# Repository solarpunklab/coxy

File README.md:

<div align="center">
<!-- ## SOLARPUNKLAB - CoXY -->

<!-- PROJECT LOGO -->

</div>

<br>

<div align="left" width = 90% id="contents">
<!-- TABLE OF CONTENTS -->
<details open>
  <summary style="background-color: #aaa;"><b>CONTENTS</b></summary>
  <ul>
	<li><a href="#about">About CoXY<br></a></li>
	<li><a href="#coxy-hardware">CoXY Hardware<br></a></li>
	<li><a href="#coxy-software">CoXY Sofwtare<br></a></li>
  </ul>
  </details>
</div>

<br><br><hr> <br><br>

<!-- >>>>>> TABLE ABOUT CoXY <<<<< -->
<table width = 90%>
<tr>
<td align = "justify" width = 90% colspan=2>
<p align="justify" id="about">
<b>ABOUT CoXY</b>
<br><br>
CoXY is a project by TeZ of 
<a href="http://solarpunklab.org">SOLARPUNK LAB</a> / 
<a href="http://hackteria.org">HACKTERIA</a> 
aimed at designing and experimenting a combined hardware and software platform that can function as a test bed for sensors' data monitoring/visualization and automation control, including motors, lights, switches and/or anything that can be driven by transistors. 
<br><br>

<br><br>
The concept arose from the collaborative efforts of Marc Dusseiller Dusjagr  and Fernando Castro, both affiliated with HACKTERIA. Their inspiration stemmed from their involvement in the GOSH Open Hardware project, where they jointly explored the design and creation of a DIY platform for Soil Respiration Chamber(SRC). See <a href="https://hackteria.org/wiki/CO2_Soil_Respiration_Chamber">Hackteria Wiki</a> for an extended overview and documentation.
<br><br>

<br><br>
TeZ and Marc reconstructed a SRC prototype at Solarpunk Lab headquarters in Amsterdam. Subsequently, TeZ embarked on experimenting with an expanded version, aiming to incorporate local sensor data monitoring via WiFi/websockets technology and mechanical parts control using motors. 
<br><br>

<br>

<br><br>
TeZ designed a printed circuit board (PCB) capable of seamlessly daisy-chaining up to five I2C devices. Additionally, it enables control over 8 channels of analog electrical signals via a transistor array IC. This is ideal to easily control the 2 coils of a 28byj-48 stepper motor with 4 channels. The PCB also features breakout options for additional ESP32 I/O pins and voltage supply.
<br><br>
</a>
This first version of the PCB is paired with a browser-based (hence cross-platform) software application, highly customizable and flexible.

<br><br>

<br><br>

<a href="#contents"></A>
<br>
</tr>
</table>

 <!-- >>>>>> TABLE CoXY HARDWARE <<<<< -->
<table width = 90%>
<tr>
<td align = "justify" width = 90% colspan=2>
<p align="justify" id="coxy-hardware">
<b>CoXY HARDWARE</b>
<br><br>
</a>
<br>
first working proto board

CoXY's test bed consists of a Lolin S2 mini ESP32 board expander that can directly interface to a ULN2803 darlington trasistor array and to the I2C bus with five onboard channels. More S2 i/o pins are exposed to connect other analog or one-wire sensors and actuators.
<br><br>
While the CoXY board was designed to reproduce a setup for Soil Respiration Chamber(s), this circuit can facilitate all kind of projects that make use of up to five I2C peripherals and up to 8 low power transistor controlled devices. The adoption of Lolin S2 Mini ESP32 board is very advantageous for the minimal size of this microcontroller, its power, the many number of i/o pins and the very convenient price too.
<br><br>

<br><br>
</tr>

<tr>

<td align = "left" width = 90% colspan=2>
<b>PARTS</b>
<br><br>
The test bed of choice for CoXY comprises:

<ul>
<li> Lolin S2 mini ESP32
<li> ULN2803 transistor array IC
<li> 28BYJ-48 stepper motor
<li> SENSIRION SCD41 - I2C Carbon Dioxide, temperature and humidity sensor
<li> BME680 - I2C temperature, humidity, pressure and gas sensor
<li> DALLAS DS18b20 "one-wire" Temperature sensor
<li> SSD1306 - 128x64 - I2C OLED display
</ul>

All parts are "optional" and can be excluded from the setup by simply commenting the #define statements in the main.cpp code. 
<br><br>
The <a href="https://github.com/GenericLab/UROS-CO2_brkout">UROS breakout</a> board was kindly provided by Marc to support the development of this project and it features also an optional connection to a NEOPIXEL rgb led unit.
<br><br>
Below all images and links to source the individual parts.
<br><br>
<nr>
LOLIN S2 Mini ESP32
<br><br>
<a href="https://nl.aliexpress.com/item/32461441516.html"><br>
ULN2803  - Bipolar (BJT) Transistor Array 8 NPN Darlington 50V 500mA </a>
<br><br>
<a href="https://nl.aliexpress.com/item/1005006141716201.html"><br>
28BYJ-48 5V stepper motor</a>
<br><br>
<a href="https://nl.aliexpress.com/item/1005006387743045.html"><br>
SCD41  I2C Carbon Dioxide, Temperature And Humidity sensor</a>
<br><br>
<a href="https://github.com/GenericLab/UROS-CO2_brkout"><br>
first SCD41 UROS breakout</a>
<br><br>
<a href="https://github.com/solarpunklab/coxy/tree/main/PCB/CO2Y-brkout"><br>
 new SCD41 CO2Y breakout</a> designed by TeZ and Marc in 2024
<br><br>
<a href="https://nl.aliexpress.com/item/1005001602441073.html"><br>
BME680 Digital Temperature, Humidity, Pressure, Gas Sensor </a>
<br><br>

<a href="https://nl.aliexpress.com/item/32676135779.html"><br>
DALLAS DS18b20 "one-wire" Temperature sensor</a>
<br><br>

<a href="https://nl.aliexpress.com/item/1005006141235306.html"><br>
SSD1306 - 128x64 - I2C OLED display</a>
<br><br>

<hr>

CoXY BOARD is a PCB designed by TeZ and currently in testing phase. More details and photos will be published soon.

<br>

<br>

<br><br>

<br><br>

<br><br>

<br><br>

<br><br>

<br><br>

<br>
<hr>
<br>
<a href="STL/CoxyBoxy.stl" target="3d"></A>
<br>
<a href="STL/CoxyBoxy-top.stl" target="3d"></A>
<br><br>
<a href="#contents"></A>
<br>

</td>
<br>
</tr>
</table>

<!-- >>>>>> TABLE CoXY SOFTWARE<<<<< -->
<table width = 90%>
<tr>
<td align = "justify" width = 90% colspan=2>
<p align="justify" id="coxy-software">
<b>CoXY SOFTWARE</b>
<br><br>
The CoXY KONTROL software is a web app served by the ESP32 developed as a combined Arduino C++, HTML5, Javascript, CSS and JSON code base. This browser-based app can therefore run on any device.
<br><br>

<br>
CoXY KONTROL dashboard
<br><br>
In order to simplify the simultaneous coding with different languages and many Arduino and Javascript libraries, VS-CODE / Platform IO was chosen as development environment. This way all the code base can be easily copied, edited and transferred at once without the need of re-configuration.
<br><br>

<br>
VS-CODE environment
<br><br>

<br>
Make sure you have PLATTFORMIO extension installed in your VS-CODE editor.
<br><br>
All files of this app are served (or created and stored in real-time) directly from the SPIFFS internal memory of the ESP32. That includes the main index.html page, the javascript code and libraries, css and json codes, images and fonts assets.
<br><br>

<br><br>
In this application the SPIFFS files occupy about 1/3 ot the total available memory. 
<br><br>

<br><br>
The esp32 sketch files "main.cpp" and "NETWORK.h" must be uploaded clicking on the arrow icon on the top right of VS-CODE window.
<br><br>

<br><br>
Once SPIFFS and sketch files are uploaded to the ESP32, and the board has connected to a local WiFi network (or it has created its own "COXY-NET" access point) we can point our browser to the URL http://coxy.local
<br><br>

<br><br>
By clicking on the S icon or hitting the 's' key the SPIFFS memory popup will open to show that status of the spiffs internal memory and the currently stored and served files.
<br><br>

<br><br>
A reading is taken every 30 seconds from all sensors at once with a timeout callback.
A progress bar shows the countdown at each reading cycle.
<br><br>

<br><br>
Data visualization is done via javascript on span elements for all sensors, except the SCD41's Co2 level, Temperature and Humidity that are shown via <a href="https://github.com/highcharts/highcharts">highcharts javascript library</a> featuring interactive data display.
<br><br>

<br><br>

<br><br>

<br><br>
A data log file with all the readings for the SCD41 is progressively saved in datalog.json file in the SPIFFS until the remaining inernal memory reaches a safety limit of 20kb. The json file can be downloaded locally by clicking on the datalog button.
<br><br>

<br><br>

<br>

<a href="#contents"></A>
<br>
</tr>
</table>

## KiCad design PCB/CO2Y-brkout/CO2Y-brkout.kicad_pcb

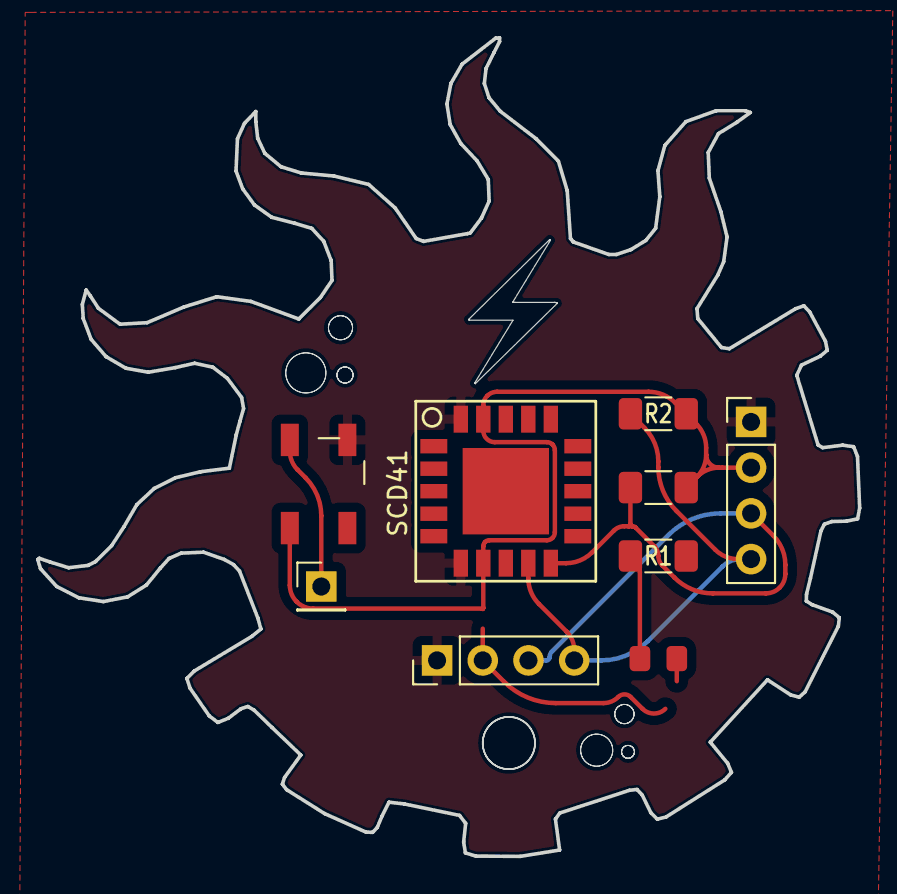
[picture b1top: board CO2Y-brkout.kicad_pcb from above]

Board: 2 copper layers, 45.7 x 45.5 mm, 14 parts (0 on the bottom side), 6 nets.

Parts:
D1: LED; LED_0805_HandSolder
D2: WS2812B; NEO-Pixel_WS2812B
J1: Conn_01x01_Pin; PinHeader_1x01_P2.54mm_Vertical
J2, J3: Conn_01x04; PinHeader_1x04_P2.54mm_Vertical
R1, R2, R3: 10k; R_1206_HandSolder
SENSIRION: LOGO; spl-outline-board
U1: SCD41; SCD41_Ada
graf2, graf3: LOGO; gas-particles-1
graf4: LOGO; CO2Y
graf5: LOGO; bubbles

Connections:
GND: D2.3 (VSS), J2.1, J3.1, R1.2, U1.6 (VSS@1), U1.20 (VSS@2)
NEO_IN: D2.4 (DIN), J1.1
unnamed: D1.1 (K), R1.1
SCL: J2.4, J3.4, R2.1, U1.9 (SCL)
SDA: J2.3, J3.3, R3.1, U1.10 (SDA)
VCC: D1.2 (A), D2.1 (VDD), J2.2, J3.2, R2.2, R3.2, U1.7 (VDD), U1.19 (VDDH)

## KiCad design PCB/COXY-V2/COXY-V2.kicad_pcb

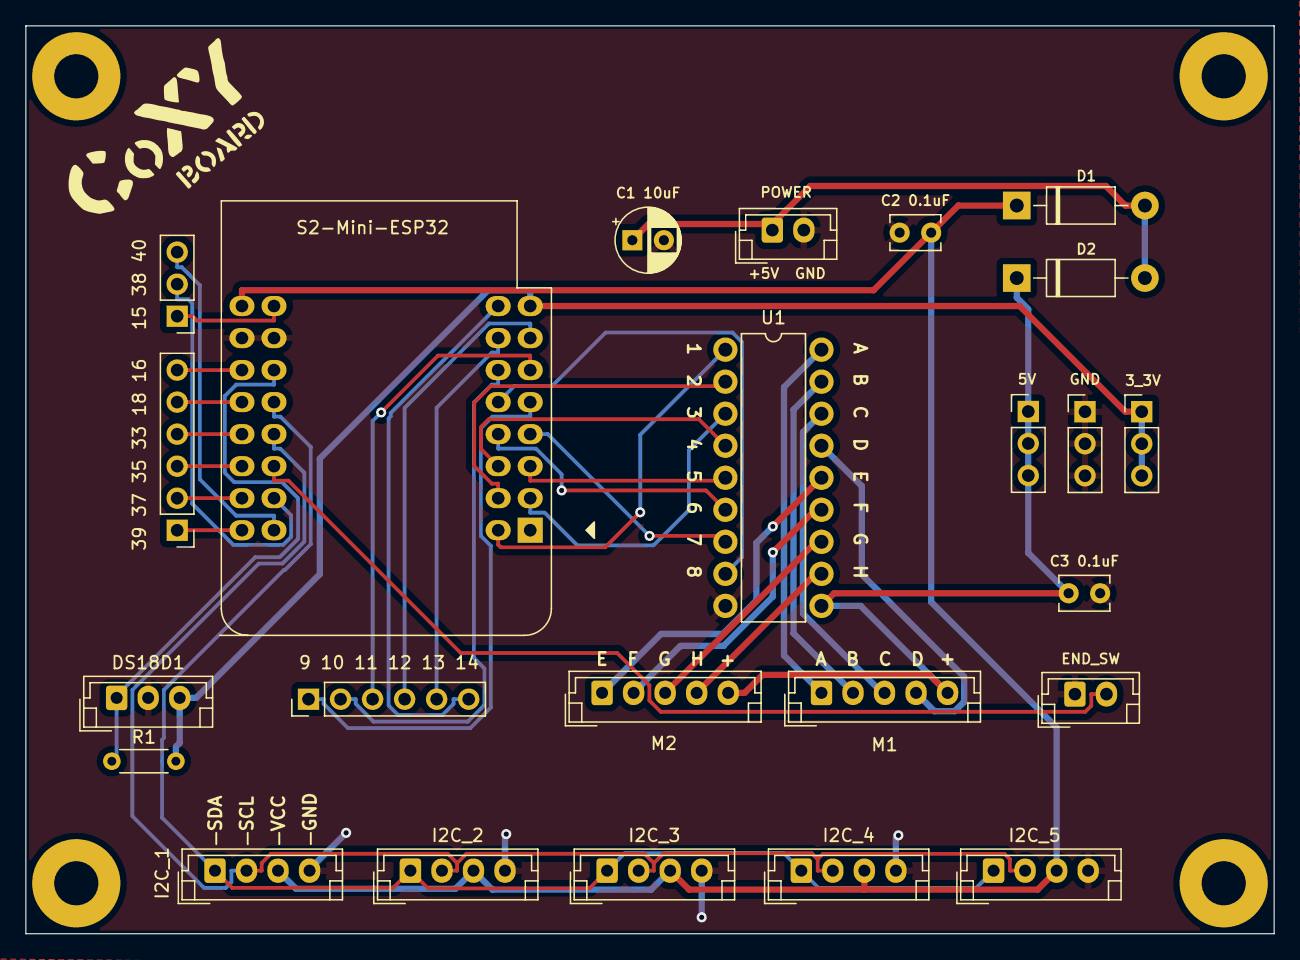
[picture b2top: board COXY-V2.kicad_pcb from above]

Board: 2 copper layers, 99.0 x 72.0 mm, 39 parts (1 on the bottom side), 40 nets.

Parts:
3_3V, 5V, 15 38 40: Conn_01x03_Socket; PinHeader_1x03_P2.54mm_Vertical
4pad_1, 4pad_2, 4pad_2#2, 4pad_3: LOGO; 4pds
9 10 11 12 13 14, 39 37 35 33 18 16: Conn_01x06_Socket; PinHeader_1x06_P2.54mm_Vertical
C1 10uF: C 10uF; CP_Radial_D5.0mm_P2.50mm
C2 0.1uF: C 01uF; C_Disc_D3.8mm_W2.6mm_P2.50mm
C3 0.1uF: C 0.1uF; C_Disc_D3.8mm_W2.6mm_P2.50mm
D1, D2: 1N4001; D_DO-41_SOD81_P10.16mm_Horizontal
DS18D1: Conn_01x03_Socket; JST_EH_B3B-EH-A_1x03_P2.50mm_Vertical
END_SW: Conn_01x02_Socket; JST_EH_B2B-EH-A_1x02_P2.50mm_Vertical
GND: Conn_01x03_Socket; PinHeader_1x03_P2.54mm_Vertical
Gn1, Gn2, Gn3: LOGO; ground-logo-mask
Gnd4: LOGO; ground-logo-mask
H1, H2, H3, H4: MountingHole; MountingHole_3.5mm_Pad
HACKTERIA: LOGO; hackteria-logo-mask
I2C_1, I2C_2, I2C_3, I2C_4, I2C_5: Conn_01x04_Socket; JST_EH_B4B-EH-A_1x04_P2.50mm_Vertical
M1, M2: Conn_01x05_Socket; JST_EH_B5B-EH-A_1x05_P2.50mm_Vertical
OSH: LOGO; osh-logo-mask
POWER: Conn_01x02_Socket; JST_EH_B2B-EH-A_1x02_P2.50mm_Vertical
R1: 4.7K; R_Axial_DIN0204_L3.6mm_D1.6mm_P5.08mm_Horizontal
S2-Mini-ESP32: LOLIN Wemos S2 Mini
SPL: LOGO; spl-logo-mask
U1: ULN2803A

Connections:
+5V: C1 10uF.1, D1.2 (A), D2.2 (A), POWER.1
DSPIN: DS18D1.1, R1.1, S2-Mini-ESP32.30 (GPIO17)
ENDSW: END_SW.2, S2-Mini-ESP32.27 (GPIO36)
GND: C1 10uF.2, C2 0.1uF.1, C3 0.1uF.2, DS18D1.2, END_SW.1, GND.1, GND.2, GND.3, I2C_1.4, I2C_2.4, I2C_3.4, I2C_4.4, I2C_5.4, POWER.2, S2-Mini-ESP32.23 (GND), S2-Mini-ESP32.31 (GND), U1.9 (GND)
IO1: S2-Mini-ESP32.9 (GPIO1), U1.1 (I1)
IO2: S2-Mini-ESP32.10 (GPIO2), U1.2 (I2)
IO3: S2-Mini-ESP32.2 (GPIO3), U1.3 (I3)
IO4: S2-Mini-ESP32.11 (GPIO4), U1.4 (I4)
IO5: S2-Mini-ESP32.3 (GPIO5), U1.5 (I5)
IO6: S2-Mini-ESP32.12 (GPIO6), U1.6 (I6)
IO7: S2-Mini-ESP32.4 (GPIO7), U1.7 (I7)
IO8: S2-Mini-ESP32.13 (GPIO8), U1.8 (I8)
IO9: 9 10 11 12 13 14.1, S2-Mini-ESP32.5 (GPIO9)
IO10: 9 10 11 12 13 14.2, S2-Mini-ESP32.14 (GPIO10)
IO11: 9 10 11 12 13 14.3, S2-Mini-ESP32.6 (GPIO11)
IO12: 9 10 11 12 13 14.4, S2-Mini-ESP32.7 (GPIO12)
IO13: 9 10 11 12 13 14.5, S2-Mini-ESP32.15 (GPIO13)
IO14: 9 10 11 12 13 14.6, S2-Mini-ESP32.16 (GPIO14)
IO15: 15 38 40.1, S2-Mini-ESP32.32 (GPIO15)
IO16: 39 37 35 33 18 16.6, S2-Mini-ESP32.22 (GPIO16)
IO18: 39 37 35 33 18 16.5, S2-Mini-ESP32.21 (GPIO18)
IO33: 39 37 35 33 18 16.4, S2-Mini-ESP32.20 (GPIO33)
IO35: 39 37 35 33 18 16.3, S2-Mini-ESP32.19 (GPIO35)
IO37: 39 37 35 33 18 16.2, S2-Mini-ESP32.18 (GPIO37)
IO38: 15 38 40.2, S2-Mini-ESP32.26 (GPIO38)
IO39: 39 37 35 33 18 16.1, S2-Mini-ESP32.17 (GPIO39)
IO40: 15 38 40.3, S2-Mini-ESP32.25 (GPIO40)
SCL: I2C_1.2, I2C_2.2, I2C_3.2, I2C_4.2, I2C_5.2, S2-Mini-ESP32.28 (GPIO34)
SDA: I2C_1.1, I2C_2.1, I2C_3.1, I2C_4.1, I2C_5.1, S2-Mini-ESP32.29 (GPIO21)
ULNOUT1: M1.1, U1.18 (O1)
ULNOUT2: M1.2, U1.17 (O2)
ULNOUT3: M1.3, U1.16 (O3)
ULNOUT4: M1.4, U1.15 (O4)
ULNOUT5: M2.1, U1.14 (O5)
ULNOUT6: M2.2, U1.13 (O6)
ULNOUT7: M2.3, U1.12 (O7)
ULNOUT8: M2.4, U1.11 (O8)
VBUS1: C2 0.1uF.2, D1.1 (K), I2C_1.3, I2C_2.3, I2C_3.3, I2C_4.3, I2C_5.3, S2-Mini-ESP32.24 (VBUS)
VBUS2: 5V.1, 5V.2, 5V.3, C3 0.1uF.1, D2.1 (K), M1.5, M2.5, U1.10 (COM)
VBUS3_3: 3_3V.1, 3_3V.2, 3_3V.3, DS18D1.3, R1.2, S2-Mini-ESP32.8 (3_3V)

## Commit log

2024-03-10 update 1
2024-03-10 update 2
2024-03-15 update easy scheme
2024-03-15 update pcb photos
2024-03-16 stl update
2024-03-19 co2y pcb gerber
2024-03-19 co2y breakout image and link
